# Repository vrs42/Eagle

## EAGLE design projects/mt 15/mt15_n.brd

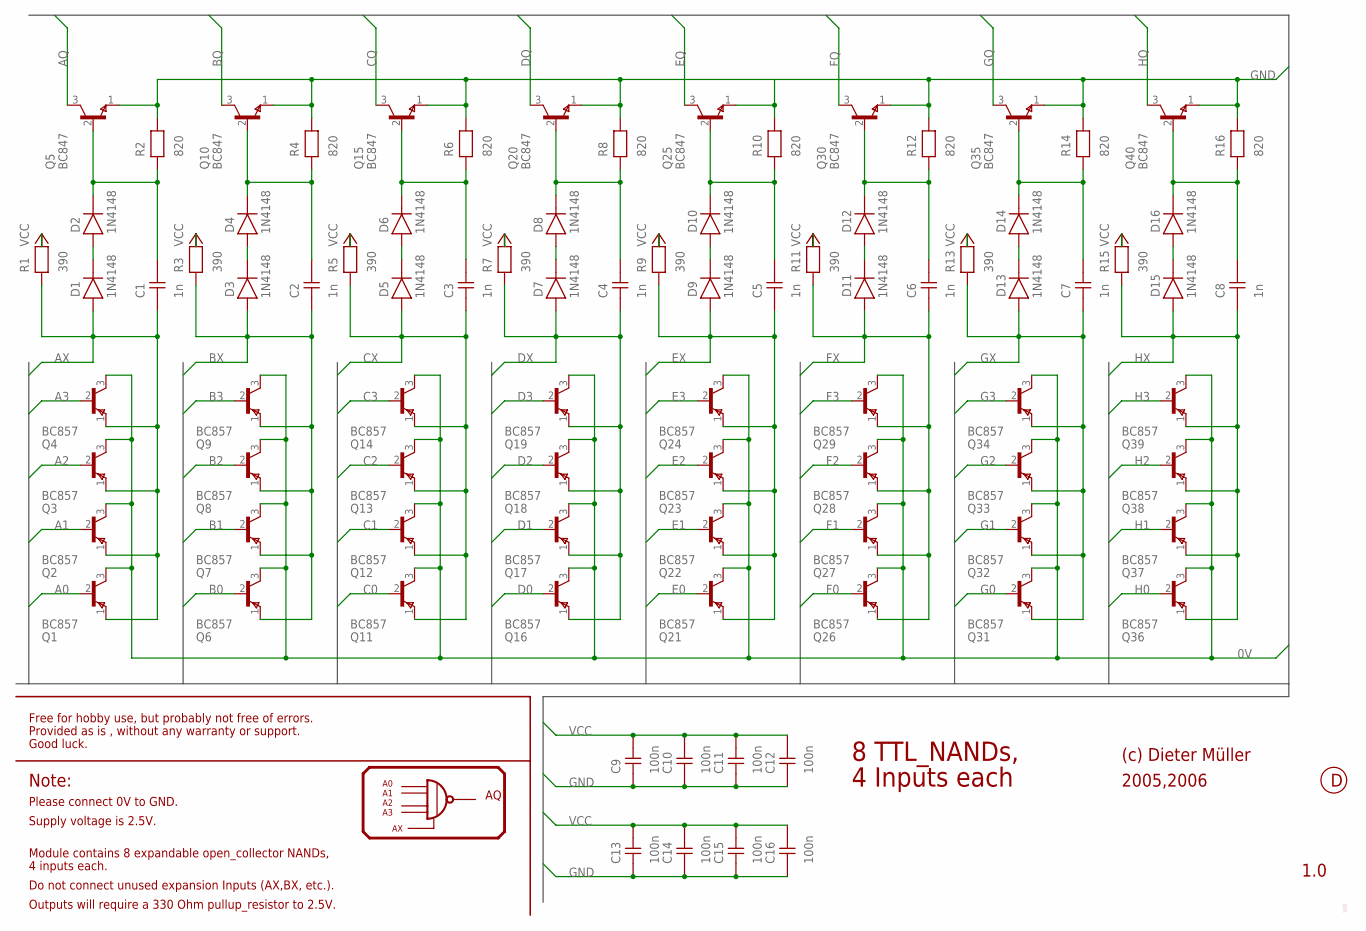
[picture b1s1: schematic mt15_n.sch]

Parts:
C1, C2, C3, C4, C5, C6, C7, C8: 1n; 0204
C9, C10, C11, C12, C13, C14, C15, C16: 100n; 0204
D1, D2, D3, D4, D5, D6, D7, D8, D9, D10, D11, D12, D13, D14, D15, D16: 1N4148; 0204D
Q1, Q2, Q3, Q4, Q6, Q7, Q8, Q9, Q11, Q12, Q13, Q14, Q16, Q17, Q18, Q19, Q21, Q22, Q23, Q24, Q26, Q27, Q28, Q29, Q31, Q32, Q33, Q34, Q36, Q37, Q38, Q39: BC857; SOT-23
Q5, Q10, Q15, Q20, Q25, Q30, Q35, Q40: BC847; SOT-23
R1, R3, R5, R7, R9, R11, R13, R15: 390; 0204
R2, R4, R6, R8, R10, R12, R14, R16: 820; 0204

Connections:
0V: Q1.3 (C), Q2.3 (C), Q3.3 (C), Q4.3 (C), Q6.3 (C), Q7.3 (C), Q8.3 (C), Q9.3 (C), Q11.3 (C), Q12.3 (C), Q13.3 (C), Q14.3 (C), Q16.3 (C), Q17.3 (C), Q18.3 (C), Q19.3 (C), Q21.3 (C), Q22.3 (C), Q23.3 (C), Q24.3 (C), Q26.3 (C), Q27.3 (C), Q28.3 (C), Q29.3 (C), Q31.3 (C), Q32.3 (C), Q33.3 (C), Q34.3 (C), Q36.3 (C), Q37.3 (C), Q38.3 (C), Q39.3 (C)
A0: Q1.2 (B)
A1: Q2.2 (B)
A2: Q3.2 (B)
A3: Q4.2 (B)
AQ: Q5.3 (C)
AX: C1.1, D1.1 (A), Q1.1 (E), Q2.1 (E), Q3.1 (E), Q4.1 (E), R1.1
B0: Q6.2 (B)
B1: Q7.2 (B)
B2: Q8.2 (B)
B3: Q9.2 (B)
BQ: Q10.3 (C)
BX: C2.1, D3.1 (A), Q6.1 (E), Q7.1 (E), Q8.1 (E), Q9.1 (E), R3.1
C0: Q11.2 (B)
C1: Q12.2 (B)
C2: Q13.2 (B)
C3: Q14.2 (B)
CQ: Q15.3 (C)
CX: C3.1, D5.1 (A), Q11.1 (E), Q12.1 (E), Q13.1 (E), Q14.1 (E), R5.1
D0: Q16.2 (B)
D1: Q17.2 (B)
D2: Q18.2 (B)
D3: Q19.2 (B)
DQ: Q20.3 (C)
DX: C4.1, D7.1 (A), Q16.1 (E), Q17.1 (E), Q18.1 (E), Q19.1 (E), R7.1
E0: Q21.2 (B)
E1: Q22.2 (B)
E2: Q23.2 (B)
E3: Q24.2 (B)
EQ: Q25.3 (C)
EX: C5.1, D9.1 (A), Q21.1 (E), Q22.1 (E), Q23.1 (E), Q24.1 (E), R9.1
F0: Q26.2 (B)
F1: Q27.2 (B)
F2: Q28.2 (B)
F3: Q29.2 (B)
FQ: Q30.3 (C)
FX: C6.1, D11.1 (A), Q26.1 (E), Q27.1 (E), Q28.1 (E), Q29.1 (E), R11.1
G0: Q31.2 (B)
G1: Q32.2 (B)
G2: Q33.2 (B)
G3: Q34.2 (B)
GND: C9.1, C10.1, C11.1, C12.1, C13.1, C14.1, C15.1, C16.1, Q5.1 (E), Q10.1 (E), Q15.1 (E), Q20.1 (E), Q25.1 (E), Q30.1 (E), Q35.1 (E), Q40.1 (E), R2.2, R4.2, R6.2, R8.2, R10.2, R12.2, R14.2, R16.2
GQ: Q35.3 (C)
GX: C7.1, D13.1 (A), Q31.1 (E), Q32.1 (E), Q33.1 (E), Q34.1 (E), R13.1
H0: Q36.2 (B)
H1: Q37.2 (B)
H2: Q38.2 (B)
H3: Q39.2 (B)
HQ: Q40.3 (C)
HX: C8.1, D15.1 (A), Q36.1 (E), Q37.1 (E), Q38.1 (E), Q39.1 (E), R15.1
unnamed: D1.2 (K), D2.1 (A)
unnamed: C1.2, D2.2 (K), Q5.2 (B), R2.1
unnamed: D3.2 (K), D4.1 (A)
unnamed: C2.2, D4.2 (K), Q10.2 (B), R4.1
unnamed: D5.2 (K), D6.1 (A)
unnamed: C3.2, D6.2 (K), Q15.2 (B), R6.1
unnamed: D7.2 (K), D8.1 (A)
unnamed: C4.2, D8.2 (K), Q20.2 (B), R8.1
unnamed: D9.2 (K), D10.1 (A)
unnamed: C5.2, D10.2 (K), Q25.2 (B), R10.1
unnamed: D11.2 (K), D12.1 (A)
unnamed: C6.2, D12.2 (K), Q30.2 (B), R12.1
unnamed: D13.2 (K), D14.1 (A)
unnamed: C7.2, D14.2 (K), Q35.2 (B), R14.1
unnamed: D15.2 (K), D16.1 (A)
unnamed: C8.2, D16.2 (K), Q40.2 (B), R16.1
VCC: C9.2, C10.2, C11.2, C12.2, C13.2, C14.2, C15.2, C16.2, R1.2, R3.2, R5.2, R7.2, R9.2, R11.2, R13.2, R15.2

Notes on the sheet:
Free for hobby use, but probably not free of errors.
Provided as is , without any warranty or support.
Good luck.
Note:
Module contains 8 expandable open_collector NANDs,
4 inputs each.
Please connect 0V to GND.
Outputs will require a 330 Ohm pullup_resistor to 2.5V.
Supply voltage is 2.5V.
(c) Dieter Müller
2005,2006
1.0
4 Inputs each
8 TTL_NANDs,
Zehn kleine Bastler fein, die löten Teile ein.
Neun kleine Bastler fein, viel Einsamkeit verbracht.
Acht kleine Bastler fein, und wo ist DOS geblieben ?
Sieben kleine Bastler fein, und Schaltungen komplex.
Sechs kleine Bastler fein, verdrehten sich die Rümpfe.
Die Bandscheiben verhakten sich, da waren's nur noch Fünfe.
Fünf kleine Bastler fein, das Internet war hier.
Vier kleine Bastler fein, verkabeln allerlei.
Drei kleine Bastler fein, bei HF gleich dabei.
Zwei kleine Bastler fein, geärgert wie sonst keiner.
Den einen traf der Herzinfarkt, und übrig bleibt noch einer.
Ein kleiner Bastler fein, das Studium vollbracht,
hat seit er auf der Arbeit baut, zuhaus' nichts mehr gemacht.
Ein klein, zwei klein, drei klein vier klein, fünf klein Bastler fein.
Sechs klein, sieben klein, acht klein, neun klein, zehn klein Bastler fein.
Denn wer sich Elektronik baut, bleibt öfters einmal liegen.
Solange es noch Spass dir macht, lass dich nicht unterkriegen.
Auch du hast keine Chance:
Zehn kleine Bastler fein...
Do not connect unused expansion Inputs (AX,BX, etc.).
Doch einen krallte sich die Post, da waren's nur noch zwei.
Und einer hat nicht aufgepasst, da waren's nur noch drei.
Sie trafen falsche Freundlichkeit, da waren's nur noch vier.
Dabei ist einer abgedreht, da waren's nur noch sechs.
Seit es nur bunte Fenster gab, da waren's nur noch sieben.
Und einer hat geheiratet, da waren's nur noch acht.

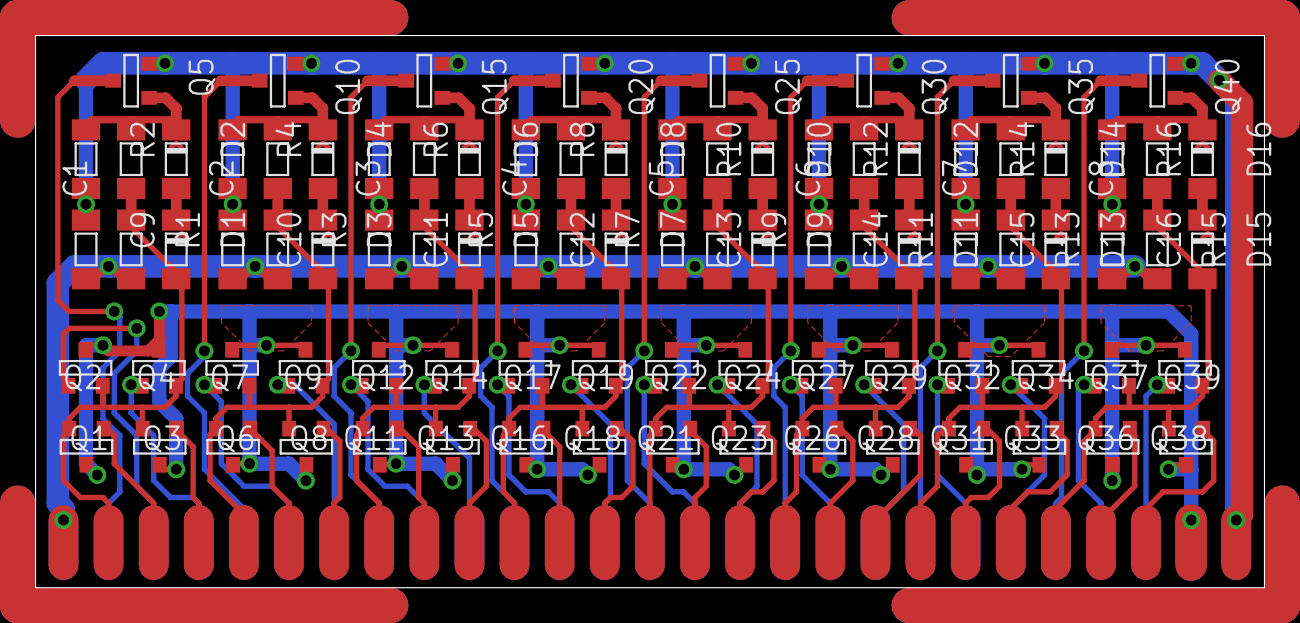
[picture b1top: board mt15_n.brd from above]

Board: 2 copper layers, 69.2 x 31.1 mm, 88 parts (0 on the bottom side), 27 nets.

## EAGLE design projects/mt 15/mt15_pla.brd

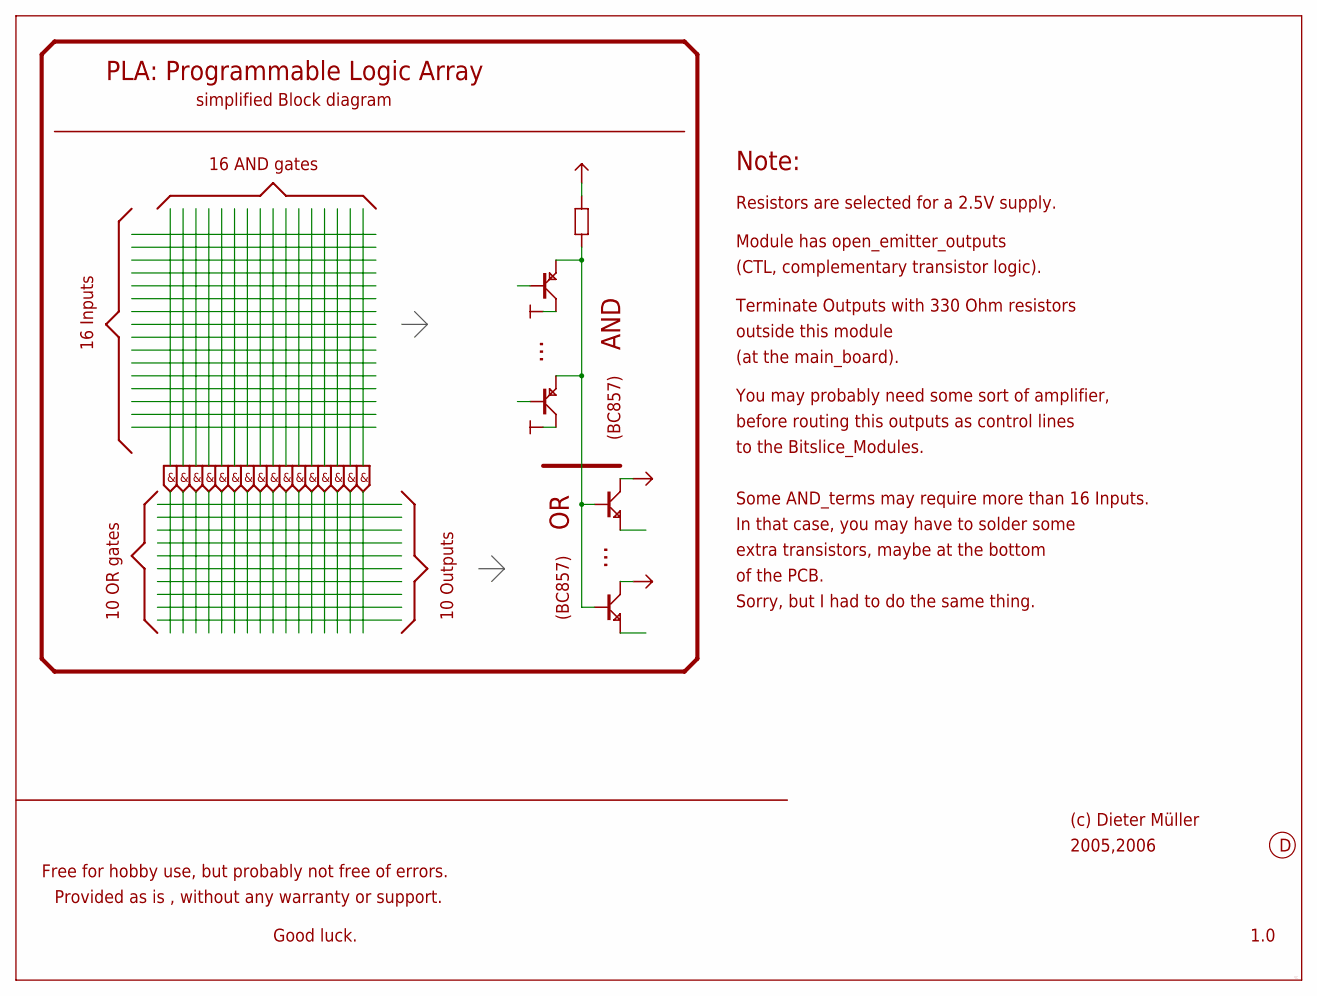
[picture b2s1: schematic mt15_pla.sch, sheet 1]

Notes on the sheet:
(c) Dieter Müller
2005,2006
1.0
Free for hobby use, but probably not free of errors.
Provided as is , without any warranty or support.
Good luck.
10 Outputs
16 AND gates
10 OR gates
AND
...
16 Inputs
(BC857)
PLA: Programmable Logic Array
simplified Block diagram
Note:
Module has open_emitter_outputs
(CTL, complementary transistor logic).
Terminate Outputs with 330 Ohm resistors
outside this module
(at the main_board).
You may probably need some sort of amplifier,
before routing this outputs as control lines
to the Bitslice_Modules.
Some AND_terms may require more than 16 Inputs.
extra transistors, maybe at the bottom
of the PCB.
Sorry, but I had to do the same thing.
Was die Politiker versprechen, ist schon toll.
Mit ihren Lügen quatschen sie den Wähler voll.
All das Reformgebrabbel und die Rangelei.
Aber ihre grösste Hoffnung ist,
dass er diesen ganzen Quatsch vergisst.
Wenn nicht, dann ist das alles nicht so schlimm.
Solang' er macht sein Kreuzchen richtig hin.
Der Wähler sitzt nur da und weint dabei.
Resistors are selected for a 2.5V supply.
In that case, you may have to solder some

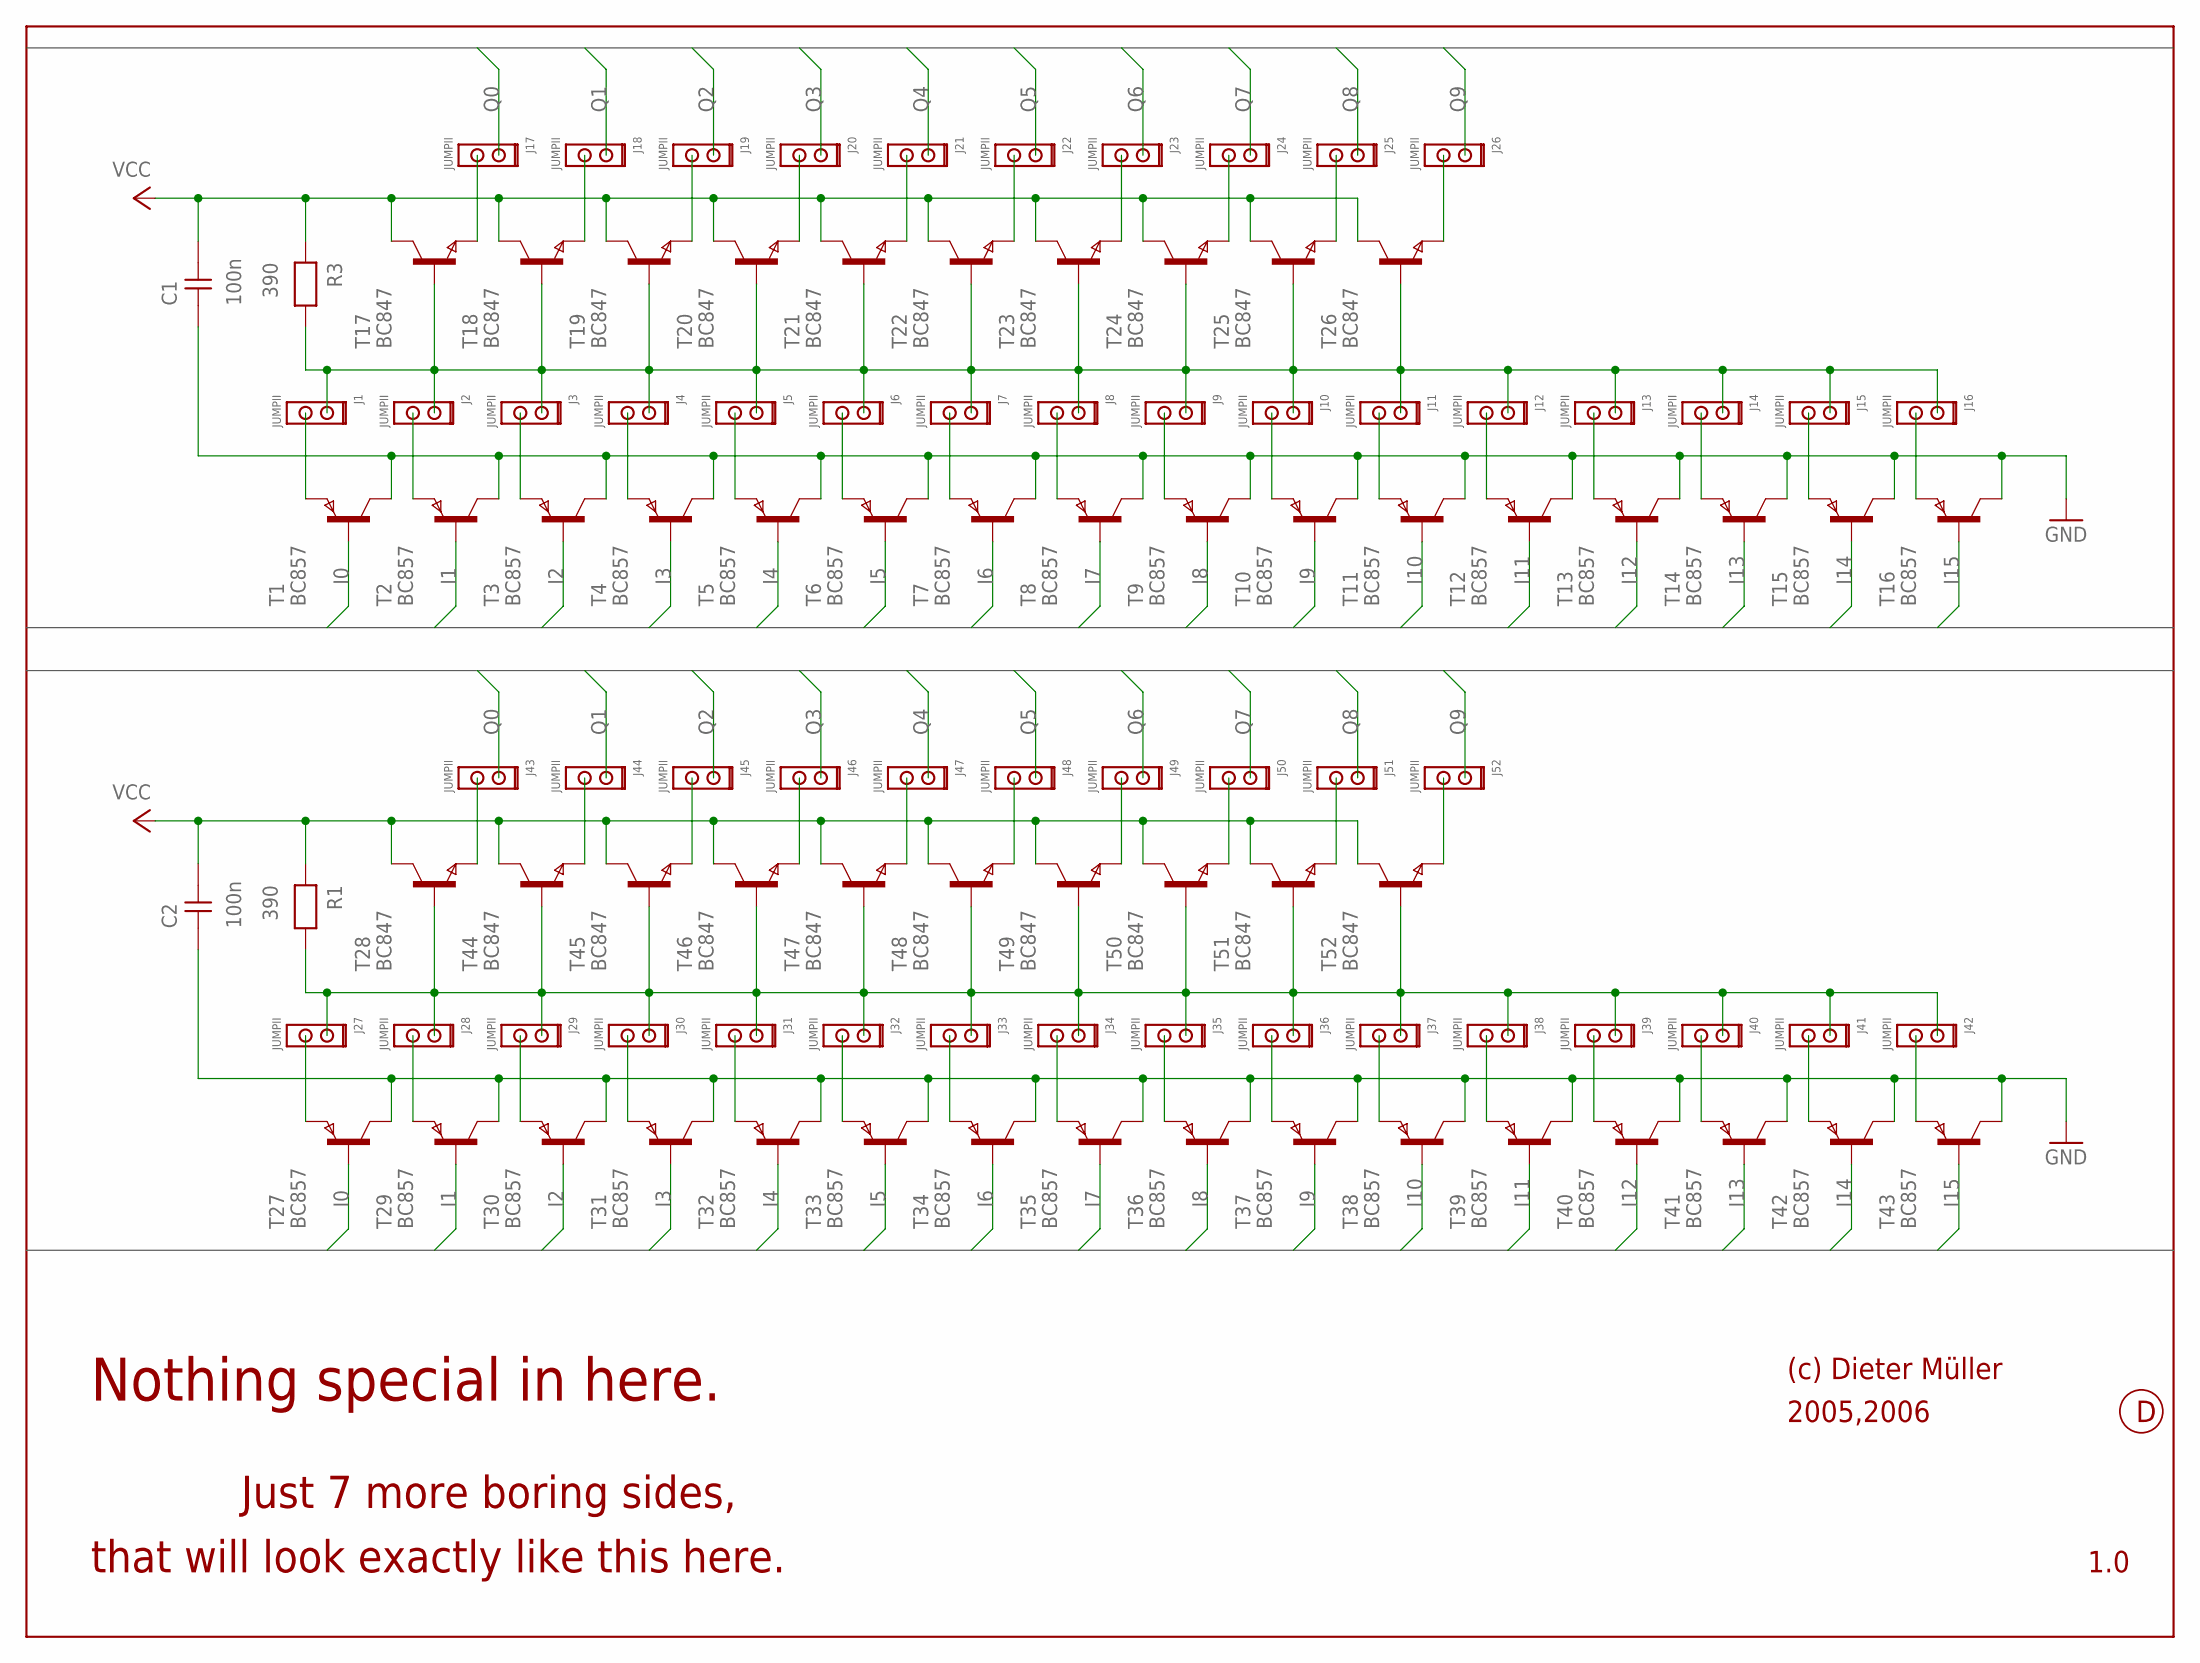
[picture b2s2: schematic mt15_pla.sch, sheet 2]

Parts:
C1, C2: 100n; 0204
J1, J2, J3, J4, J5, J6, J7, J8, J9, J10, J11, J12, J13, J14, J15, J16, J17, J18, J19, J20, J21, J22, J23, J24, J25, J26, J27, J28, J29, J30, J31, J32, J33, J34, J35, J36, J37, J38, J39, J40, J41, J42, J43, J44, J45, J46, J47, J48, J49, J50, J51, J52: JUMPII
R1, R3: 390; 0204
T1, T2, T3, T4, T5, T6, T7, T8, T9, T10, T11, T12, T13, T14, T15, T16, T27, T29, T30, T31, T32, T33, T34, T35, T36, T37, T38, T39, T40, T41, T42, T43: BC857; SOT-23
T17, T18, T19, T20, T21, T22, T23, T24, T25, T26, T28, T44, T45, T46, T47, T48, T49, T50, T51, T52: BC847; SOT-23

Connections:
GND: C1.1, C2.1, T1.3 (C), T2.3 (C), T3.3 (C), T4.3 (C), T5.3 (C), T6.3 (C), T7.3 (C), T8.3 (C), T9.3 (C), T10.3 (C), T11.3 (C), T12.3 (C), T13.3 (C), T14.3 (C), T15.3 (C), T16.3 (C), T27.3 (C), T29.3 (C), T30.3 (C), T31.3 (C), T32.3 (C), T33.3 (C), T34.3 (C), T35.3 (C), T36.3 (C), T37.3 (C), T38.3 (C), T39.3 (C), T40.3 (C), T41.3 (C), T42.3 (C), T43.3 (C); also elsewhere on the board
I0: T1.2 (B), T27.2 (B); also elsewhere on the board
I1: T2.2 (B), T29.2 (B); also elsewhere on the board
I2: T3.2 (B), T30.2 (B); also elsewhere on the board
I3: T4.2 (B), T31.2 (B); also elsewhere on the board
I4: T5.2 (B), T32.2 (B); also elsewhere on the board
I5: T6.2 (B), T33.2 (B); also elsewhere on the board
I6: T7.2 (B), T34.2 (B); also elsewhere on the board
I7: T8.2 (B), T35.2 (B); also elsewhere on the board
I8: T9.2 (B), T36.2 (B); also elsewhere on the board
I9: T10.2 (B), T37.2 (B); also elsewhere on the board
I10: T11.2 (B), T38.2 (B); also elsewhere on the board
I11: T12.2 (B), T39.2 (B); also elsewhere on the board
I12: T13.2 (B), T40.2 (B); also elsewhere on the board
I13: T14.2 (B), T41.2 (B); also elsewhere on the board
I14: T15.2 (B), T42.2 (B); also elsewhere on the board
I15: T16.2 (B), T43.2 (B); also elsewhere on the board
unnamed: J1.2, T1.1 (E)
unnamed: J2.2, T2.1 (E)
unnamed: J3.2, T3.1 (E)
unnamed: J1.1, J2.1, J3.1, J4.1, J5.1, J6.1, J7.1, J8.1, J9.1, J10.1, J11.1, J12.1, J13.1, J14.1, J15.1, J16.1, R3.2, T17.2 (B), T18.2 (B), T19.2 (B), T20.2 (B), T21.2 (B), T22.2 (B), T23.2 (B), T24.2 (B), T25.2 (B), T26.2 (B)
unnamed: J16.2, T16.1 (E)
unnamed: J15.2, T15.1 (E)
unnamed: J14.2, T14.1 (E)
unnamed: J13.2, T13.1 (E)
unnamed: J12.2, T12.1 (E)
unnamed: J6.2, T6.1 (E)
unnamed: J5.2, T5.1 (E)
unnamed: J4.2, T4.1 (E)
unnamed: J7.2, T7.1 (E)
unnamed: J8.2, T8.1 (E)
unnamed: J9.2, T9.1 (E)
unnamed: J10.2, T10.1 (E)
unnamed: J11.2, T11.1 (E)
unnamed: J27.2, T27.1 (E)
unnamed: J28.2, T29.1 (E)
unnamed: J29.2, T30.1 (E)
unnamed: J27.1, J28.1, J29.1, J30.1, J31.1, J32.1, J33.1, J34.1, J35.1, J36.1, J37.1, J38.1, J39.1, J40.1, J41.1, J42.1, R1.2, T28.2 (B), T44.2 (B), T45.2 (B), T46.2 (B), T47.2 (B), T48.2 (B), T49.2 (B), T50.2 (B), T51.2 (B), T52.2 (B)
unnamed: J42.2, T43.1 (E)
unnamed: J41.2, T42.1 (E)
unnamed: J26.2, T26.1 (E)
unnamed: J17.2, T17.1 (E)
unnamed: J18.2, T18.1 (E)
unnamed: J19.2, T19.1 (E)
unnamed: J20.2, T20.1 (E)
unnamed: J21.2, T21.1 (E)
unnamed: J22.2, T22.1 (E)
unnamed: J23.2, T23.1 (E)
unnamed: J24.2, T24.1 (E)
unnamed: J25.2, T25.1 (E)
unnamed: J40.2, T41.1 (E)
unnamed: J39.2, T40.1 (E)
unnamed: J38.2, T39.1 (E)
unnamed: J32.2, T33.1 (E)
unnamed: J31.2, T32.1 (E)
unnamed: J30.2, T31.1 (E)
unnamed: J33.2, T34.1 (E)
unnamed: J34.2, T35.1 (E)
unnamed: J35.2, T36.1 (E)
unnamed: J36.2, T37.1 (E)
unnamed: J37.2, T38.1 (E)
unnamed: J52.2, T52.1 (E)
unnamed: J43.2, T28.1 (E)
unnamed: J44.2, T44.1 (E)
unnamed: J45.2, T45.1 (E)
unnamed: J46.2, T46.1 (E)
unnamed: J47.2, T47.1 (E)
unnamed: J48.2, T48.1 (E)
unnamed: J49.2, T49.1 (E)
unnamed: J50.2, T50.1 (E)
unnamed: J51.2, T51.1 (E)
Q0: J17.1, J43.1; also elsewhere on the board
Q1: J18.1, J44.1; also elsewhere on the board
Q2: J19.1, J45.1; also elsewhere on the board
Q3: J20.1, J46.1; also elsewhere on the board
Q4: J21.1, J47.1; also elsewhere on the board
Q5: J22.1, J48.1; also elsewhere on the board
Q6: J23.1, J49.1; also elsewhere on the board
Q7: J24.1, J50.1; also elsewhere on the board
Q8: J25.1, J51.1; also elsewhere on the board
Q9: J26.1, J52.1; also elsewhere on the board
VCC: C1.2, C2.2, R1.1, R3.1, T17.3 (C), T18.3 (C), T19.3 (C), T20.3 (C), T21.3 (C), T22.3 (C), T23.3 (C), T24.3 (C), T25.3 (C), T26.3 (C), T28.3 (C), T44.3 (C), T45.3 (C), T46.3 (C), T47.3 (C), T48.3 (C), T49.3 (C), T50.3 (C), T51.3 (C), T52.3 (C); also elsewhere on the board

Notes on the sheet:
(c) Dieter Müller
2005,2006
1.0
Nothing special in here.
Just 7 more boring sides,
that will look exactly like this here.

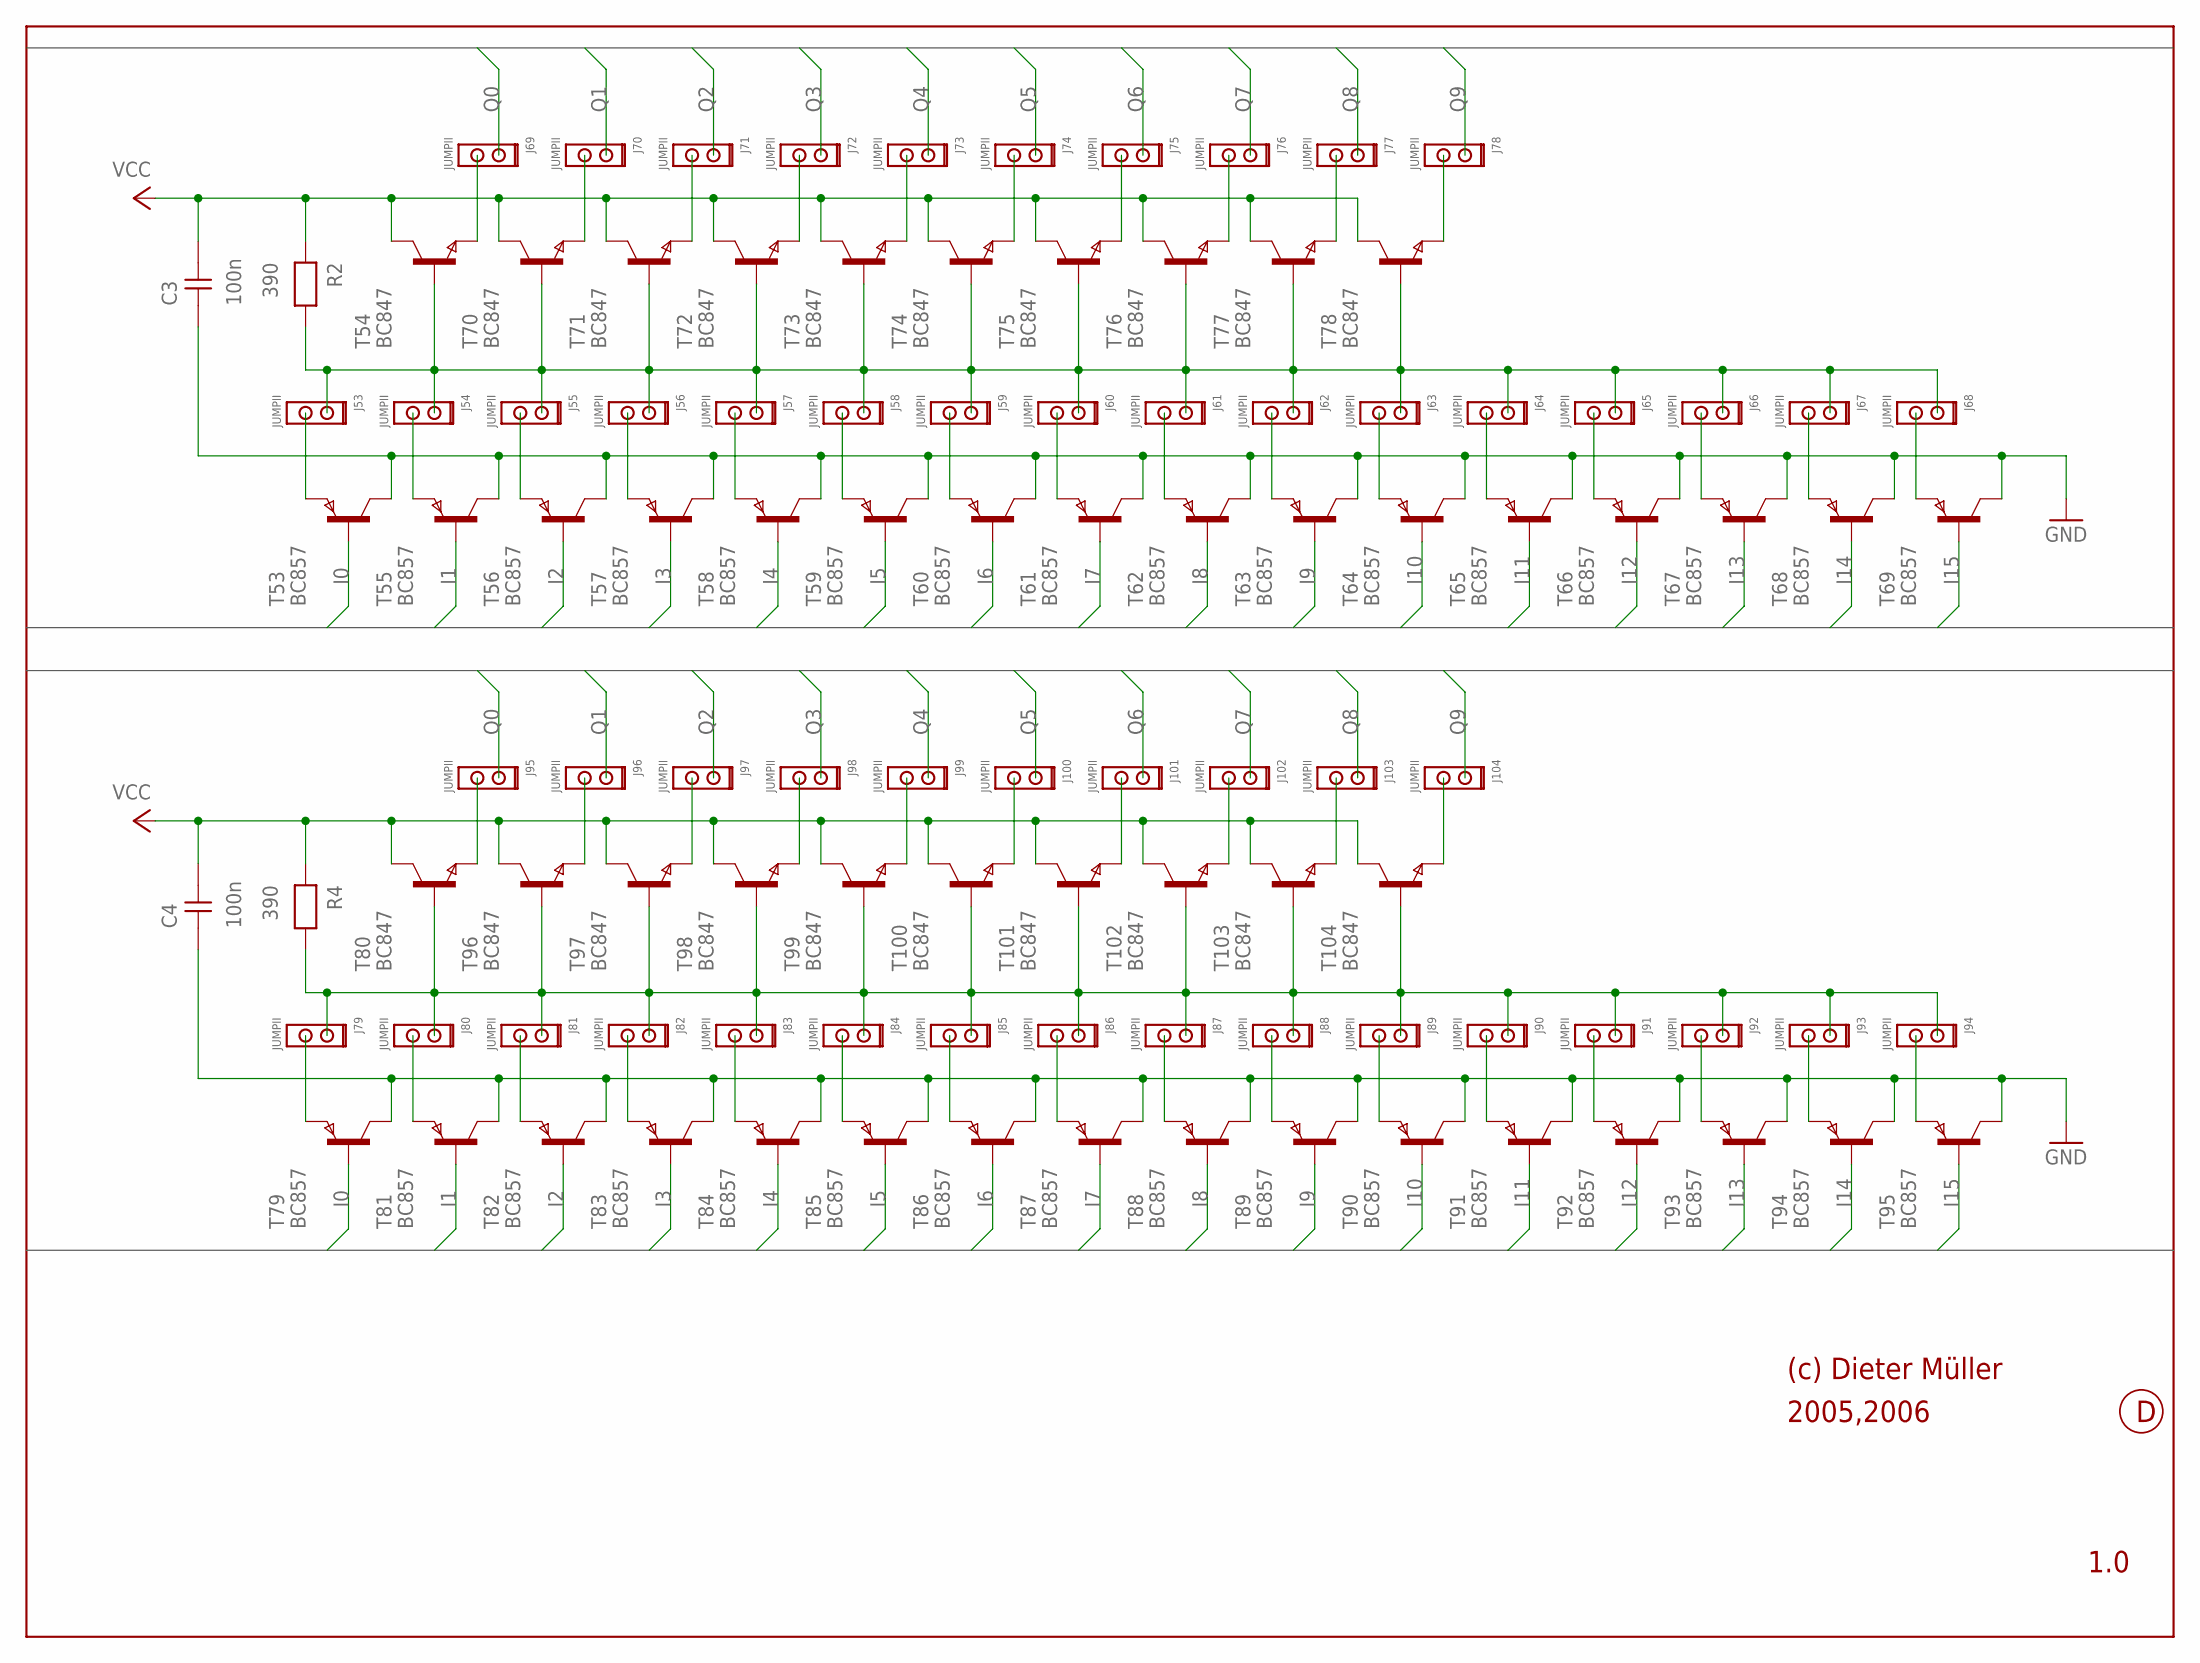
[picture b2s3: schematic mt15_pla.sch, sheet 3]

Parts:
C3, C4: 100n; 0204
J53, J54, J55, J56, J57, J58, J59, J60, J61, J62, J63, J64, J65, J66, J67, J68, J69, J70, J71, J72, J73, J74, J75, J76, J77, J78, J79, J80, J81, J82, J83, J84, J85, J86, J87, J88, J89, J90, J91, J92, J93, J94, J95, J96, J97, J98, J99, J100, J101, J102, J103, J104: JUMPII
R2, R4: 390; 0204
T53, T55, T56, T57, T58, T59, T60, T61, T62, T63, T64, T65, T66, T67, T68, T69, T79, T81, T82, T83, T84, T85, T86, T87, T88, T89, T90, T91, T92, T93, T94, T95: BC857; SOT-23
T54, T70, T71, T72, T73, T74, T75, T76, T77, T78, T80, T96, T97, T98, T99, T100, T101, T102, T103, T104: BC847; SOT-23

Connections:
GND: C3.1, C4.1, T53.3 (C), T55.3 (C), T56.3 (C), T57.3 (C), T58.3 (C), T59.3 (C), T60.3 (C), T61.3 (C), T62.3 (C), T63.3 (C), T64.3 (C), T65.3 (C), T66.3 (C), T67.3 (C), T68.3 (C), T69.3 (C), T79.3 (C), T81.3 (C), T82.3 (C), T83.3 (C), T84.3 (C), T85.3 (C), T86.3 (C), T87.3 (C), T88.3 (C), T89.3 (C), T90.3 (C), T91.3 (C), T92.3 (C), T93.3 (C), T94.3 (C), T95.3 (C); also elsewhere on the board
I0: T53.2 (B), T79.2 (B); also elsewhere on the board
I1: T55.2 (B), T81.2 (B); also elsewhere on the board
I2: T56.2 (B), T82.2 (B); also elsewhere on the board
I3: T57.2 (B), T83.2 (B); also elsewhere on the board
I4: T58.2 (B), T84.2 (B); also elsewhere on the board
I5: T59.2 (B), T85.2 (B); also elsewhere on the board
I6: T60.2 (B), T86.2 (B); also elsewhere on the board
I7: T61.2 (B), T87.2 (B); also elsewhere on the board
I8: T62.2 (B), T88.2 (B); also elsewhere on the board
I9: T63.2 (B), T89.2 (B); also elsewhere on the board
I10: T64.2 (B), T90.2 (B); also elsewhere on the board
I11: T65.2 (B), T91.2 (B); also elsewhere on the board
I12: T66.2 (B), T92.2 (B); also elsewhere on the board
I13: T67.2 (B), T93.2 (B); also elsewhere on the board
I14: T68.2 (B), T94.2 (B); also elsewhere on the board
I15: T69.2 (B), T95.2 (B); also elsewhere on the board
unnamed: J53.2, T53.1 (E)
unnamed: J54.2, T55.1 (E)
unnamed: J55.2, T56.1 (E)
unnamed: J53.1, J54.1, J55.1, J56.1, J57.1, J58.1, J59.1, J60.1, J61.1, J62.1, J63.1, J64.1, J65.1, J66.1, J67.1, J68.1, R2.2, T54.2 (B), T70.2 (B), T71.2 (B), T72.2 (B), T73.2 (B), T74.2 (B), T75.2 (B), T76.2 (B), T77.2 (B), T78.2 (B)
unnamed: J68.2, T69.1 (E)
unnamed: J67.2, T68.1 (E)
unnamed: J66.2, T67.1 (E)
unnamed: J65.2, T66.1 (E)
unnamed: J64.2, T65.1 (E)
unnamed: J58.2, T59.1 (E)
unnamed: J57.2, T58.1 (E)
unnamed: J56.2, T57.1 (E)
unnamed: J59.2, T60.1 (E)
unnamed: J60.2, T61.1 (E)
unnamed: J61.2, T62.1 (E)
unnamed: J62.2, T63.1 (E)
unnamed: J63.2, T64.1 (E)
unnamed: J78.2, T78.1 (E)
unnamed: J69.2, T54.1 (E)
unnamed: J70.2, T70.1 (E)
unnamed: J71.2, T71.1 (E)
unnamed: J72.2, T72.1 (E)
unnamed: J73.2, T73.1 (E)
unnamed: J74.2, T74.1 (E)
unnamed: J75.2, T75.1 (E)
unnamed: J76.2, T76.1 (E)
unnamed: J77.2, T77.1 (E)
unnamed: J79.2, T79.1 (E)
unnamed: J80.2, T81.1 (E)
unnamed: J81.2, T82.1 (E)
unnamed: J79.1, J80.1, J81.1, J82.1, J83.1, J84.1, J85.1, J86.1, J87.1, J88.1, J89.1, J90.1, J91.1, J92.1, J93.1, J94.1, R4.2, T80.2 (B), T96.2 (B), T97.2 (B), T98.2 (B), T99.2 (B), T100.2 (B), T101.2 (B), T102.2 (B), T103.2 (B), T104.2 (B)
unnamed: J94.2, T95.1 (E)
unnamed: J93.2, T94.1 (E)
unnamed: J92.2, T93.1 (E)
unnamed: J91.2, T92.1 (E)
unnamed: J90.2, T91.1 (E)
unnamed: J84.2, T85.1 (E)
unnamed: J83.2, T84.1 (E)
unnamed: J82.2, T83.1 (E)
unnamed: J85.2, T86.1 (E)
unnamed: J86.2, T87.1 (E)
unnamed: J87.2, T88.1 (E)
unnamed: J88.2, T89.1 (E)
unnamed: J89.2, T90.1 (E)
unnamed: J104.2, T104.1 (E)
unnamed: J95.2, T80.1 (E)
unnamed: J96.2, T96.1 (E)
unnamed: J97.2, T97.1 (E)
unnamed: J98.2, T98.1 (E)
unnamed: J99.2, T99.1 (E)
unnamed: J100.2, T100.1 (E)
unnamed: J101.2, T101.1 (E)
unnamed: J102.2, T102.1 (E)
unnamed: J103.2, T103.1 (E)
Q0: J69.1, J95.1; also elsewhere on the board
Q1: J70.1, J96.1; also elsewhere on the board
Q2: J71.1, J97.1; also elsewhere on the board
Q3: J72.1, J98.1; also elsewhere on the board
Q4: J73.1, J99.1; also elsewhere on the board
Q5: J74.1, J100.1; also elsewhere on the board
Q6: J75.1, J101.1; also elsewhere on the board
Q7: J76.1, J102.1; also elsewhere on the board
Q8: J77.1, J103.1; also elsewhere on the board
Q9: J78.1, J104.1; also elsewhere on the board
VCC: C3.2, C4.2, R2.1, R4.1, T54.3 (C), T70.3 (C), T71.3 (C), T72.3 (C), T73.3 (C), T74.3 (C), T75.3 (C), T76.3 (C), T77.3 (C), T78.3 (C), T80.3 (C), T96.3 (C), T97.3 (C), T98.3 (C), T99.3 (C), T100.3 (C), T101.3 (C), T102.3 (C), T103.3 (C), T104.3 (C); also elsewhere on the board

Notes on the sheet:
(c) Dieter Müller
2005,2006
1.0
